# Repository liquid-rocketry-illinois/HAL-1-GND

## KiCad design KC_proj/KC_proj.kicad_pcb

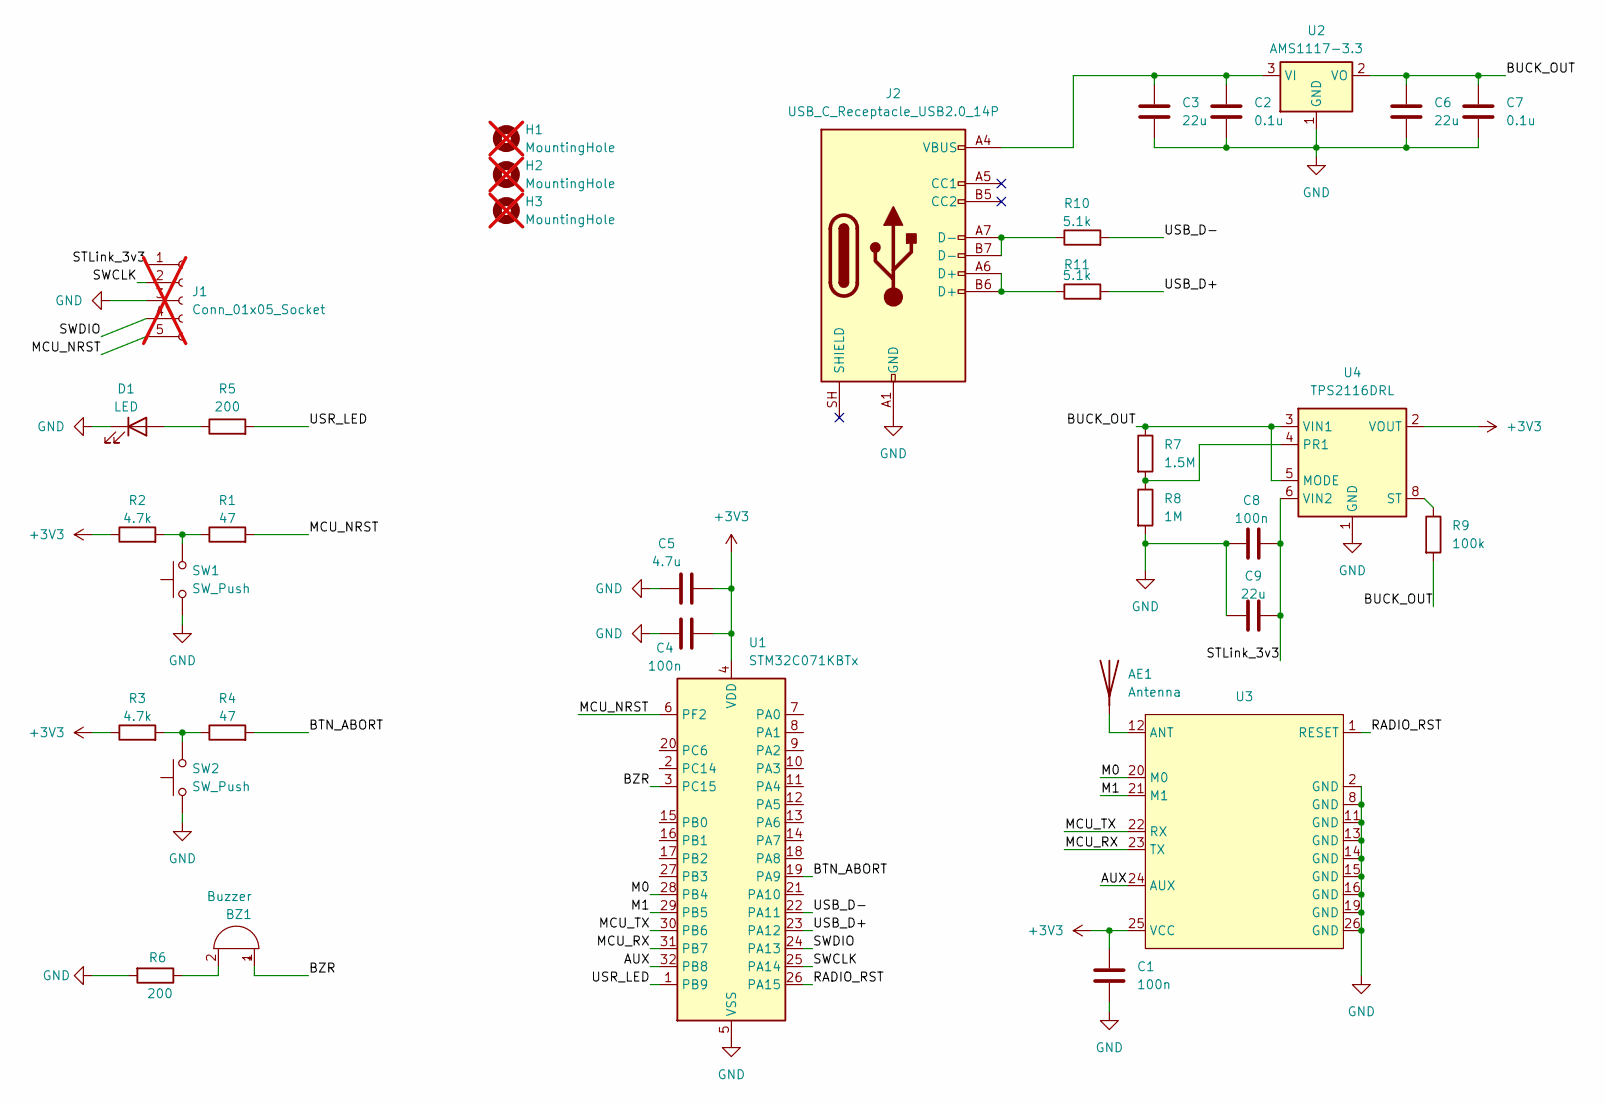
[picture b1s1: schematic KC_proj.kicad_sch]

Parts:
AE1: Antenna; SMA_Amphenol_901-143_Horizontal
BZ1: Buzzer; Buzzer_12x9.5RM7.6
C1, C4, C8: 100n; C_0603_1608Metric
C2, C7: 0.1u; C_0603_1608Metric
C3, C6, C9: 22u; C_0603_1608Metric
C5: 4.7u; C_0603_1608Metric
D1: LED; LED_0603_1608Metric
H1, H2, H3: MountingHole; MountingHole_2.2mm_M2; not fitted
J1: Conn_01x05_Socket; PinHeader_1x05_P2.54mm_Vertical; not fitted
J2: USB_C_Receptacle_USB2.0_14P; USB_C_Receptacle_HRO_TYPE-C-31-M-12
R1, R4: 47; R_0603_1608Metric
R2, R3: 4.7k; R_0603_1608Metric
R5, R6: 200; R_0603_1608Metric
R7: 1.5M; R_0603_1608Metric
R8: 1M; R_0603_1608Metric
R9: 100k; R_0603_1608Metric
R10, R11: 5.1k; R_0603_1608Metric
SW1, SW2: SW_Push; SW_Push_1P1T_NO_CK_KSC6xxJ
U1: STM32C071KBTx; LQFP-32_7x7mm_P0.8mm
U2: AMS1117-3.3; SOT-223-3_TabPin2
U3: E22-900T22S
U4: TPS2116DRL; SOT-583-8

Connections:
+3V3: C1.1, C4.2, C5.2, R2.1, R3.1, U1.4 (VDD), U3.25 (VCC), U4.2 (VOUT), U4.7 (VOUT)
/AUX: U1.32 (PB8), U3.24 (AUX)
/BTN_ABORT: R4.2, U1.19 (PA9)
/BUCK_OUT: C6.1, C7.1, R7.1, R9.2, U2.2 (VO), U4.3 (VIN1), U4.5 (MODE)
/BZR: BZ1.1 (+), U1.3 (PC15)
/M0: U1.28 (PB4), U3.20 (M0)
/M1: U1.29 (PB5), U3.21 (M1)
/MCU_NRST: J1.5, R1.2, U1.6 (PF2)
/MCU_RX: U1.31 (PB7), U3.23 (TX)
/MCU_TX: U1.30 (PB6), U3.22 (RX)
/RADIO_RST: U1.26 (PA15), U3.1 (RESET)
/STLink_3v3: C8.2, C9.2, J1.1, U4.6 (VIN2)
/SWCLK: J1.2, U1.25 (PA14)
/SWDIO: J1.4, U1.24 (PA13)
/USB_D+: R11.2, U1.23 (PA12)
/USB_D-: R10.2, U1.22 (PA11)
/USR_LED: R5.2, U1.1 (PB9)
GND: C1.2, C2.2, C3.2, C4.1, C5.1, C6.2, C7.2, C8.1, C9.1, D1.1 (K), J1.3, J2.A1 (GND), J2.A12 (GND), J2.B1 (GND), J2.B12 (GND), R6.2, R8.2, SW1.1, SW2.1, U1.5 (VSS), U2.1 (GND), U3.2 (GND), U3.8 (GND), U3.11 (GND), U3.13 (GND), U3.14 (GND), U3.15 (GND), U3.16 (GND), U3.19 (GND), U3.26 (GND), U4.1 (GND)
unnamed: AE1.1 (A_1), U3.12 (ANT)
unnamed: BZ1.2 (-), R6.1
unnamed: D1.2 (A), R5.1
unnamed: J2.A6 (D+), J2.B6 (D+), R11.1
unnamed: J2.A7 (D-), J2.B7 (D-), R10.1
unnamed: R1.1, R2.2, SW1.2
unnamed: R3.2, R4.1, SW2.2
unnamed: C2.1, C3.1, J2.A4 (VBUS), J2.A9 (VBUS), J2.B4 (VBUS), J2.B9 (VBUS), U2.3 (VI)
unnamed: R7.2, R8.1, U4.4 (PR1)
unnamed: R9.1, U4.8 (ST)

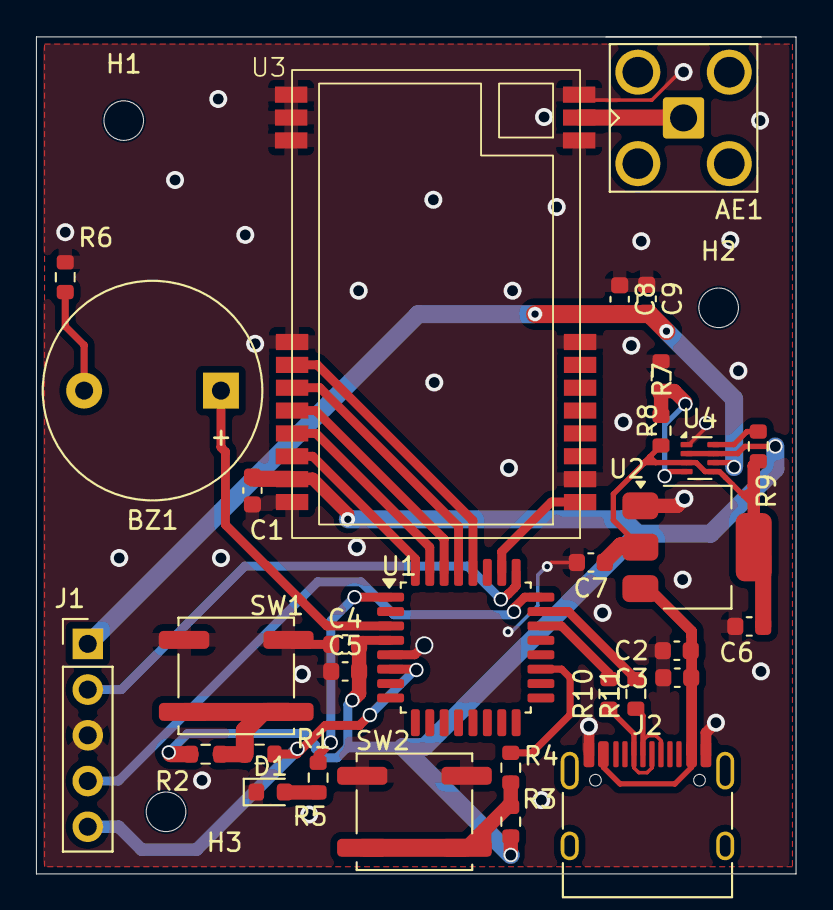
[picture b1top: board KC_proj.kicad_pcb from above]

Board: 2 copper layers, 42.2 x 46.5 mm, 34 parts (0 on the bottom side), 28 nets.

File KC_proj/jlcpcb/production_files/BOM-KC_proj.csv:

Comment,Designator,Footprint,LCSC,Quantity
0.1u,"C2,C7",C_0603_1608Metric,C14663,2
1.5M,R7,R_0603_1608Metric,C2930143,1
100k,R9,R_0603_1608Metric,C25803,1
100n,"C1,C4,C8",C_0603_1608Metric,C14663,3
1M,R8,R_0603_1608Metric,C22935,1
200,"R5,R6",R_0603_1608Metric,C8218,2
22u,"C3,C6,C9",C_0603_1608Metric,C59461,3
4.7k,"R2,R3",R_0603_1608Metric,C23162,2
4.7u,C5,C_0603_1608Metric,C19666,1
47,"R1,R4",R_0603_1608Metric,C23182,2
5.1k,"R10,R11",R_0603_1608Metric,C23186,2
AMS1117-3.3,U2,SOT-223-3_TabPin2,C6186,1
Antenna,AE1,SMA_Amphenol_901-143_Horizontal,C429844,1
Buzzer,BZ1,Buzzer_12x9.5RM7.6,C96222,1
STM32C071KBTx,U1,LQFP-32_7x7mm_P0.8mm,C42116633,1
SW_Push,"SW1,SW2",SW_Push_1P1T_NO_CK_KSC6xxJ,C455118,2
TPS2116DRL,U4,SOT-583-8,C3235557,1
~,U3,E22-900T22S,C411289,1
LED,D1,LED_0603_1608Metric,,1
USB_C_Receptacle_USB2.0_14P,J2,USB_C_Receptacle_HRO_TYPE-C-31-M-12,,1

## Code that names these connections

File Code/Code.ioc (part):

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Mcu.Name=STM32C071KBTx
Mcu.Package=LQFP32_GP
Mcu.UserName=STM32C071KBTx
PA11\ [PA9].Mode=Device
PA11\ [PA9].Signal=USB_DM
PA12\ [PA10].Mode=Device
PA12\ [PA10].Signal=USB_DP
PA13.Mode=Serial_Wire
PA13.Signal=DEBUG_SWDIO
PA14-BOOT0.Mode=Serial_Wire
PA14-BOOT0.Signal=DEBUG_SWCLK
PA15.GPIOParameters=GPIO_Label
PA15.GPIO_Label=RADIO_RST
PA15.Signal=GPIO_Output
PA9.GPIOParameters=GPIO_Label
PA9.GPIO_Label=BTN_ABORT
PA9.Signal=GPIO_Input
PB4.GPIOParameters=GPIO_Label
PB4.GPIO_Label=RADIO_M0
PB4.Signal=GPIO_Output
PB5.GPIOParameters=GPIO_Label
PB5.GPIO_Label=RADIO_M1
PB5.Signal=GPIO_Output
PB6.GPIOParameters=GPIO_Speed,GPIO_Label
PB6.GPIO_Label=MCU_TX
PB6.GPIO_Speed=GPIO_SPEED_FREQ_VERY_HIGH
PB6.Mode=Asynchronous
PB6.Signal=USART1_TX
PB7.GPIOParameters=GPIO_Speed,GPIO_Label
PB7.GPIO_Label=MCU_RX
PB7.GPIO_Speed=GPIO_SPEED_FREQ_VERY_HIGH
PB7.Mode=Asynchronous
PB7.Signal=USART1_RX
PB8.GPIOParameters=GPIO_Label
PB8.GPIO_Label=RADIO_AUX
PB8.Signal=GPIO_Input
PB9.GPIOParameters=GPIO_Label
PB9.GPIO_Label=USR_LED
PB9.Signal=GPIO_Output
PC15-OSCX_OUT(PC15).GPIOParameters=GPIO_Label
PC15-OSCX_OUT(PC15).GPIO_Label=BZR
PC15-OSCX_OUT(PC15).Signal=GPIO_Output
PF2-NRST.GPIOParameters=GPIO_Label
PF2-NRST.GPIO_Label=MCU_NRST
PF2-NRST.Signal=GPIO_Input
RCC.HSE_VALUE=8000000
RCC.SYSCLKFreq_VALUE=48000000
board=custom

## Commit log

2026-04-24 Upload kicad stuff
2026-04-24 Generated code + libraries
2026-04-24 wire kicad diags
2026-05-01 Remake Cmake project with new MCU. Finish PCB Design v1 for review.
2026-05-01 Make mounting holes excluded
2026-05-08 Update libs and kicad
2026-05-13 add tare structure
2026-05-13 Build project as v1.0
2026-05-15 Add buzzer test
2026-05-15 check tusb
2026-05-15 upload usb test code
2026-05-18 debug radio code
2026-05-19 latch estop procedure
2026-05-19 slow air data rate for higher range
2026-05-20 Add extra RSSI byte. Update logic to retreive local RSSI
2026-05-23 Update structure, resolve RCI connection issue
2026-05-24 Fix RSSI byte position in config
2026-05-26 Update receiving data end sync byte placement
2026-05-27 Upload transmission non-disrupt send-receive protocol test
2026-05-28 Update tinyusb, tweak RSSI send function to match RCI
2026-06-01 Fix radio packet byte reception issue
2026-06-04 Update servo actuation data transceive
2026-06-08 update sending logic for longer bursts and fewer interrupts to fc
2026-06-12 gps debug in progress
2026-06-12 Fix RSSI Local byte to output RSSI during data recieve
2026-06-17 flight
2026-06-18 implement remote frequency change v1
2026-06-18 implement remote frequency change v2
